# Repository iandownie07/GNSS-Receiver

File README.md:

# GNSS-Receiver
Prototype PCB to receive GNSS signals to measure ocean wave spectra. 4-layer board includes UBLOX MAX-M10S and Taoglas antenna connected with impedance-controlled grounded waveguide.

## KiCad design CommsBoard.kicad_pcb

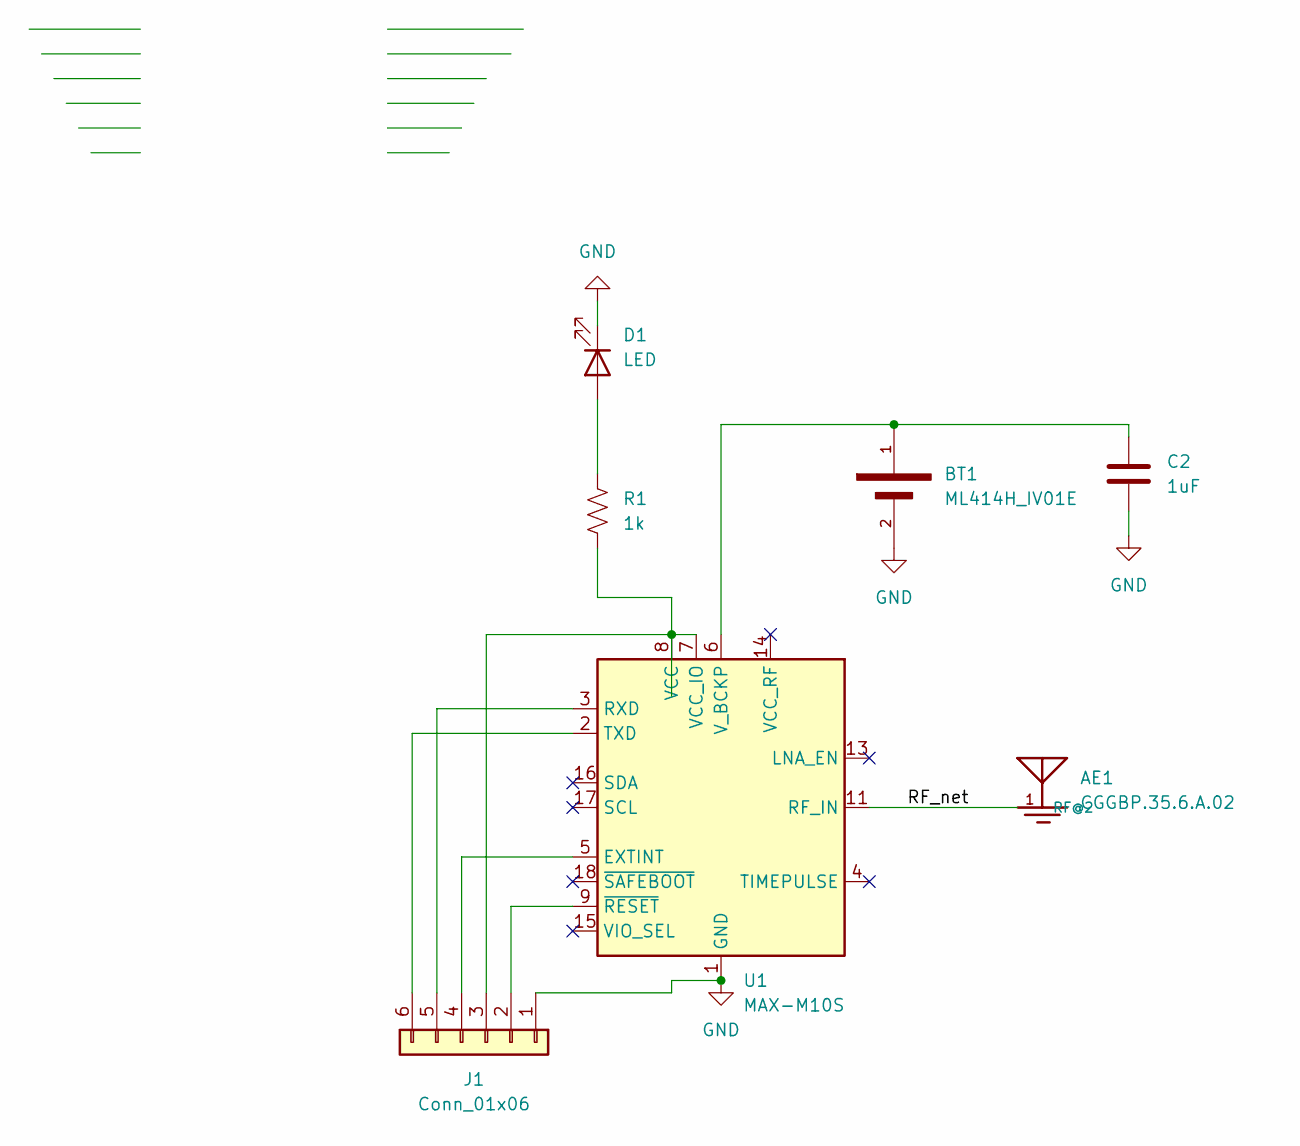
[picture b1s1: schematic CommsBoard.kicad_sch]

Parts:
AE1: CGGBP.35.6.A.02; XCVR_CGGBP.35.6.A.02
BT1: ML414H_IV01E; SEIKO_ML414H_IV01E
C2: 1uF; C_1210_3225Metric_Pad1.33x2.70mm_HandSolder
D1: LED; LED_1206_3216Metric_Pad1.42x1.75mm_HandSolder
J1: Conn_01x06; PinHeader_1x06_P2.54mm_Vertical
R1: 1k; R_1206_3216Metric_Pad1.30x1.75mm_HandSolder
U1: MAX-M10S; ublox_MAX

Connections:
/RF_net: AE1.1 (RF@2), U1.11 (RF_IN)
GND: BT1.2, C2.2, D1.1 (K), J1.1, U1.1 (GND), U1.10 (GND), U1.12 (GND)
unnamed: D1.2 (A), R1.1
unnamed: J1.2, U1.9 (~RESET)
unnamed: J1.3, R1.2, U1.7 (VCC_IO), U1.8 (VCC)
unnamed: J1.4, U1.5 (EXTINT)
unnamed: J1.5, U1.3 (RXD)
unnamed: J1.6, U1.2 (TXD)
unnamed: BT1.1, C2.1, U1.6 (V_BCKP)

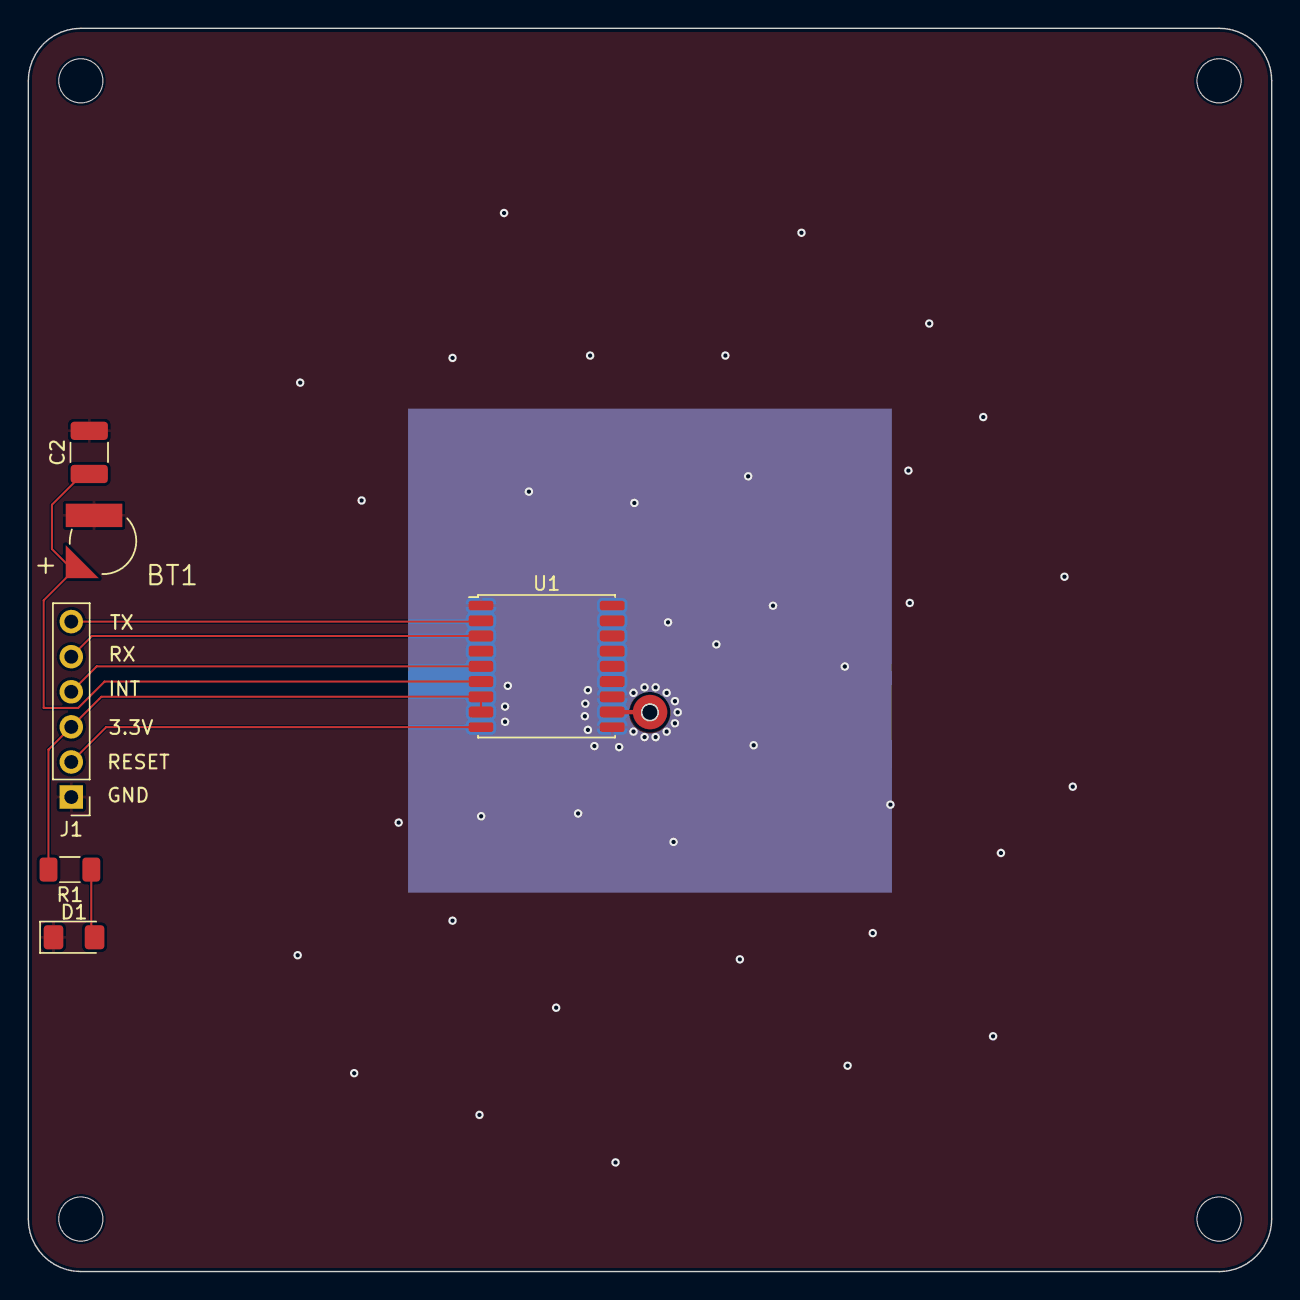
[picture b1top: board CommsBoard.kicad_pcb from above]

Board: 4 copper layers, 90.0 x 90.0 mm, 7 parts (1 on the bottom side), 9 nets.

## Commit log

2025-07-23 add files
2025-07-23 readme
